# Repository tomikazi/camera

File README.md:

# Overview
The project provides a high-quality and low-latency video stream using Raspberry Pi HQ camera while allowing control of 
the camera orientation on pan & tilt axes. The video stream can be viewed using any modern browser or mobile device.
The camera orientation can be controlled using several different means. On mobile devices, it can be controlled using
touch swipe gestures or by moving the mobile device in 3D space. On desktop or laptop computers, the keyboard or mouse
drag gestures can be used.

The project is an adaptation of the [131/h264-live-player](https://github.com/131/h264-live-player) project. It differs
from the original project in number of ways, with the most important distinction being that the camera code is structured
as a client that connects to a broker, which is capable of brokering connections to multiple cameras and allows
multiple viewers to view the same camera.

This arrangement is better suited for deployment of cameras behind firewalls.

The video stream from the camera can be viewed on any modern browser. The pan/tilt can be controlled using several 
different means.

* Using mouse click-and-drag or tap-and-drag on touch devices
* Using arrow keyboard keys and other keyboard short-cuts  
* Using mobile device motion - works for iOS devices and select Androids that support `DeviceMotionEvent` Web API
    * Note that this requires the broker to use HTTPS

The pan and tilt mechanism uses A4988 stepper drivers and NEMA 17 motors to move about a Raspberry Pi HQ camera.
The current mount design allows for -180/+180 degrees on pan axis and -50/+50 degrees on tilt axis. Two hall-effect
sensors are used as limit sensors to allow for auto-homing the mount.

Note that this adaptation mangles the original by removing the alternate forms of streaming, instead focusing
solely on supporting the `raspvid` live stream.

# Installation of Broker Software
The broker is required as it is the only means of acquiring the video stream. For simple setup, it can be installed on
the same Raspberry Pi as the camera software. 

```
# Install or update the camera broker software
curl -s https://raw.githubusercontent.com/tomikazi/camera/master/tools/install-broker.sh | sh

# Setup the camera broker software to run as a daemon
curl -s https://raw.githubusercontent.com/tomikazi/camera/master/tools/install-broker-service.sh | sudo sh
```

Once started, the broker will listen on port 6000 for incoming WebSocket connections from the cameras and on port 5000 
for incoming HTTP requests and WebSocket connections from viewers. To expose HTTPS, it's probably easiest to use Apache 2
and setup redirect using URL re-writing. (_TODO: Add docs on this_)

# Installation of Camera Software
Use the following steps to install or update the camera software:

```
# Install or update the camera software
curl -s https://raw.githubusercontent.com/tomikazi/camera/master/tools/install-camera.sh | sh

# Setup the camera software to run as a daemon
curl -s https://raw.githubusercontent.com/tomikazi/camera/master/tools/install-camera-service.sh | sudo sh -s CAMERA-NAME [BROKER-URL]
```

Once started, the software will trigger auto-homing sequence and attempt WebSocket connection on port 6000 to the broker.
After the connection is established, the `raspivid` will be spawned and its video stream will be sent over the WebSocket
to the broker, from where it can be sent to the current viewers, be recorded or processed in some manner.

# Simple Token Authorization
The broker supports a simple token-based authorization scheme that allows securing access to the camera streams so that
only the users that know the camera name and a valid access token can access the video stream.

To enable the scheme, create a `tokens` file in the directory where the broker is installed. The format of the file
is as follows:

```
# userName: cameraName token
tom: FrontYard c11559d8-e91c-4140-85f0-9e14b4744e7e
tom: BackYard 329f1a1b-5c8d-40ab-9148-434f84312821
tom: Driveway 7a247b22-7bd8-4b27-8e1c-404fea90b615
guest: FrontYard 4ceb02b3-a0e9-4989-b1ff-72c3aac973ae
guest: Driveway a5217204-133d-4b39-900f-2222c962b535
```
The token is expected to be the standard 36 character UUID (see `uuidgen`). Presently, the user name is not used for
anything other than token management via the provided `ptcam-auth` script, which has the following usage:

```
usage: ptcam-auth <camera> list
       ptcam-auth <camera> <name>
       ptcam-auth <camera> grant <name>
       ptcam-auth <camera> revoke <name>
```

# Launching Viewer
To view a particular camera video stream, simply connect to the broker URL on port 5000 and specify the camera name and 
if security is required, the camera token, e.g.:

```
http://192.168.1.79:5000/camera/?id=FrontYard&t=c11559d8-e91c-4140-85f0-9e14b4744e7e
```

This will provide the web-page with the video stream canvas. The following is an example of the GUI when viewed on an
iOS device and with the camera positions shortcut menu activated:

The pan/tilt position and range indicator box is shown at the bottom and will be visible only when the camera is in motion.
You can see a brief [demo of the camera operation on YouTube](https://youtu.be/4mN1LiofYqg).

# REST API
The broker also supports a simple [REST API](/docs/api.md) using which other applications can query and control the remote cameras.

# Design
Additional design documentation for the 3D-printed mount, custom PCB and overall assembly can is available in the [Design](docs/design.md) section

# Credits to the original h264 project authors
* [131](mailto:131.js@cloudyks.org)
* [Broadway](https://github.com/mbebenita/Broadway)
* [urbenlegend/WebStreamer](https://github.com/urbenlegend/WebStreamer)

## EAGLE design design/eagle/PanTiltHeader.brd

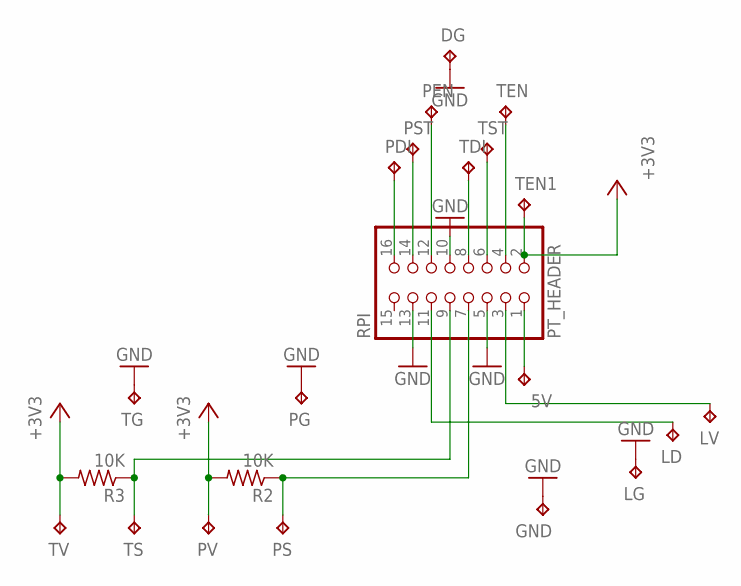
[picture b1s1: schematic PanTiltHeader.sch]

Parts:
5V: TPPAD1-13Y; P1-13Y
DG: TPPAD1-13Y; P1-13Y
GND: TPPAD1-13Y; P1-13Y
LD: TPPAD1-13Y; P1-13Y
LG: TPPAD1-13Y; P1-13Y
LV: TPPAD1-13Y; P1-13Y
PDI: TPPAD1-13Y; P1-13Y
PEN: TPPAD1-13Y; P1-13Y
PG: TPPAD1-13Y; P1-13Y
PS: TPPAD1-13Y; P1-13Y
PST: TPPAD1-13Y; P1-13Y
PT_HEADER: RPI; 2X08
PV: TPPAD1-13Y; P1-13Y
R2, R3: 10K; 0204/7
TDI: TPPAD1-13Y; P1-13Y
TEN, TEN1: TPPAD1-13Y; P1-13Y
TG: TPPAD1-13Y; P1-13Y
TS: TPPAD1-13Y; P1-13Y
TST: TPPAD1-13Y; P1-13Y
TV: TPPAD1-13Y; P1-13Y

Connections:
+3V3: PT_HEADER.2, PV.TP, R2.2, R3.2, TEN1.TP, TV.TP
GND: DG.TP, GND.TP, LG.TP, PG.TP, PT_HEADER.5, PT_HEADER.10, PT_HEADER.13, TG.TP
unnamed: PT_HEADER.4, TEN.TP
unnamed: PT_HEADER.6, TST.TP
unnamed: PT_HEADER.8, TDI.TP
unnamed: PT_HEADER.9, R3.1, TS.TP
unnamed: PEN.TP, PT_HEADER.12
unnamed: PST.TP, PT_HEADER.14
unnamed: PDI.TP, PT_HEADER.16
unnamed: 5V.TP, PT_HEADER.1
unnamed: LV.TP, PT_HEADER.3
unnamed: PS.TP, PT_HEADER.7, R2.1
unnamed: LD.TP, PT_HEADER.11

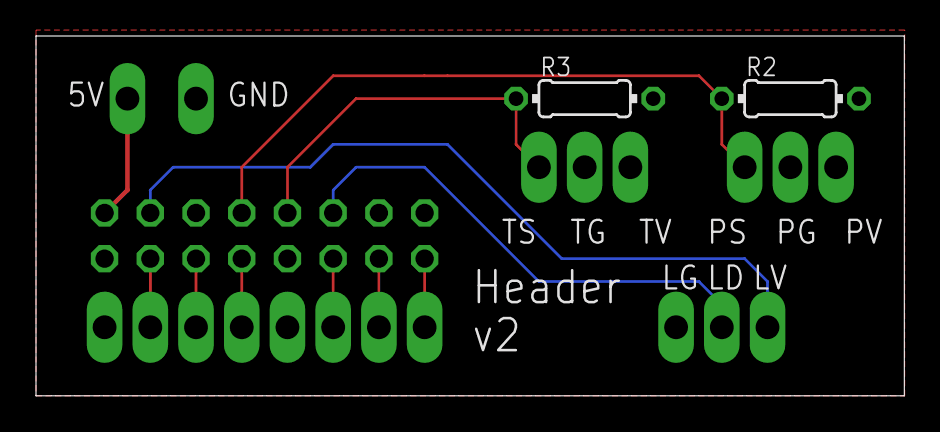
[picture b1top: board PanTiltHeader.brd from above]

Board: 2 copper layers, 48.2 x 20.0 mm, 22 parts (1 on the bottom side), 13 nets.

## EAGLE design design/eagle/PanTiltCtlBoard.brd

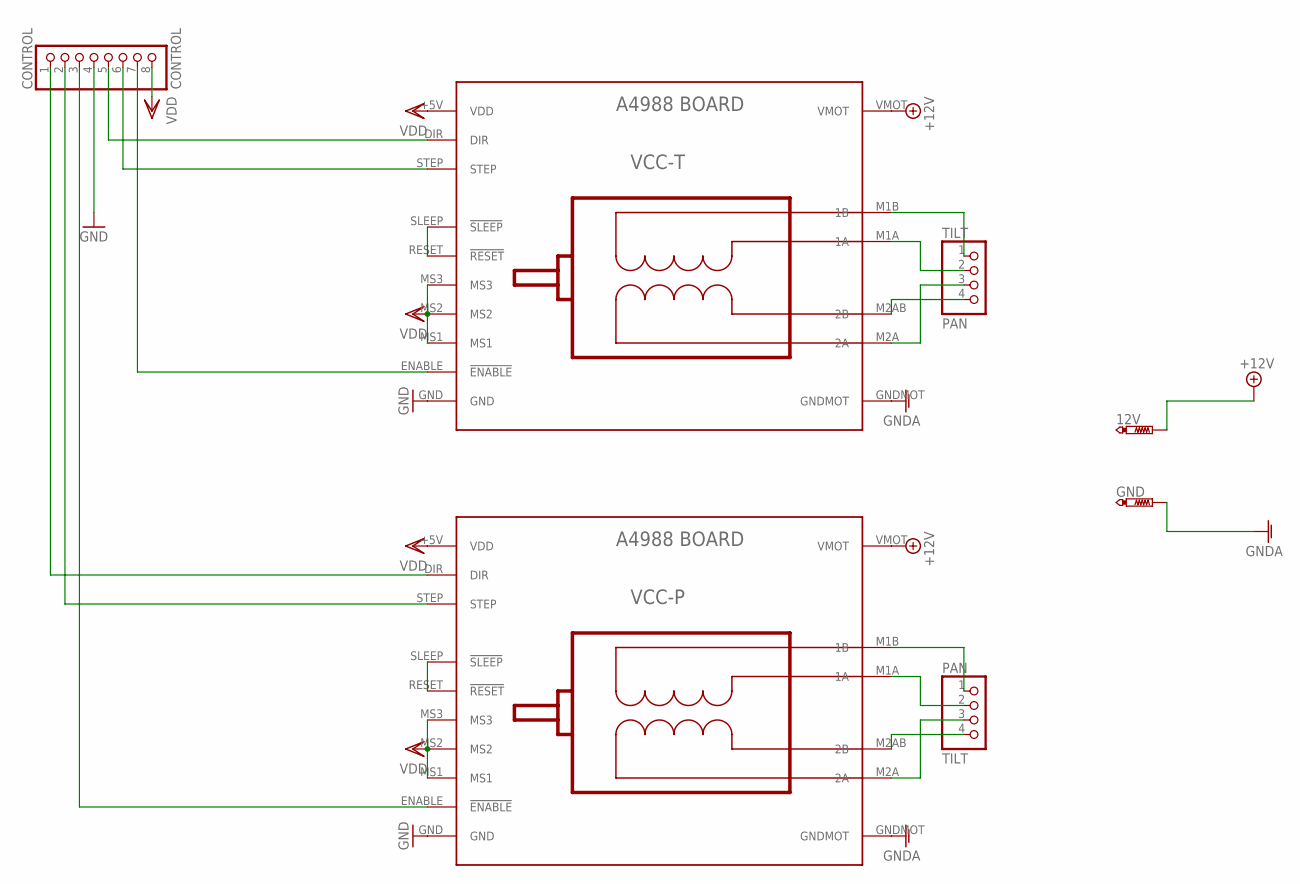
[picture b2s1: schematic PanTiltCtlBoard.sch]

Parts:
12V: PTR1PAD1-13Y; P1-13Y
CONTROL: CONTROL; 1X08
GND: PTR1PAD1-13Y; P1-13Y
PAN: TILT; 1X04
TILT: PAN; 1X04
VCC-P: BOARD_A4988
VCC-T: BOARD_A4988

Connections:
+12V: 12V.TP, VCC-P.VMOT, VCC-T.VMOT
GND: CONTROL.4, VCC-P.GND, VCC-T.GND
GNDA: GND.TP, VCC-P.GNDMOT, VCC-T.GNDMOT
unnamed: TILT.4, VCC-T.M2AB (2B)
unnamed: VCC-T.RESET (!RESET), VCC-T.SLEEP (!SLEEP)
unnamed: CONTROL.7, VCC-T.ENABLE (!ENABLE)
unnamed: CONTROL.6, VCC-T.STEP
unnamed: CONTROL.5, VCC-T.DIR
unnamed: CONTROL.1, VCC-P.DIR
unnamed: CONTROL.2, VCC-P.STEP
unnamed: CONTROL.3, VCC-P.ENABLE (!ENABLE)
unnamed: VCC-P.RESET (!RESET), VCC-P.SLEEP (!SLEEP)
unnamed: TILT.3, VCC-T.M2A (2A)
unnamed: TILT.1, VCC-T.M1B (1B)
unnamed: TILT.2, VCC-T.M1A (1A)
unnamed: PAN.4, VCC-P.M2AB (2B)
unnamed: PAN.3, VCC-P.M2A (2A)
unnamed: PAN.1, VCC-P.M1B (1B)
unnamed: PAN.2, VCC-P.M1A (1A)
VDD: CONTROL.8, VCC-P.+5V (VDD), VCC-P.MS1, VCC-P.MS2, VCC-P.MS3, VCC-T.+5V (VDD), VCC-T.MS1, VCC-T.MS2, VCC-T.MS3

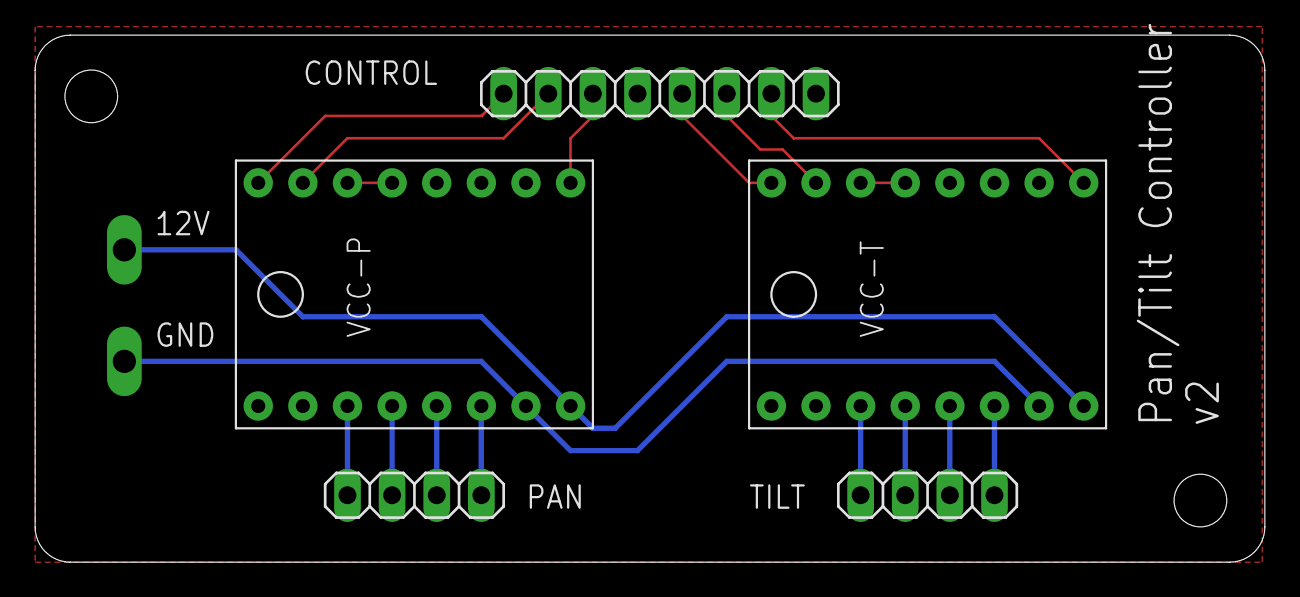
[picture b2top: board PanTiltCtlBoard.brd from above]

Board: 2 copper layers, 70.0 x 30.0 mm, 7 parts (0 on the bottom side), 20 nets.

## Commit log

2021-04-08 Initial commit; port from h264-live-player fork
2021-04-08 Renamed client to camera
2021-04-08 Adding install script for camera
2021-04-08 Adding installation scripts.
2021-04-08 Fixing broker service install
2021-04-08 More install tools tweaks.
2021-04-08 Fixed run-dev tools.
2021-04-08 Added auto-hiding of the position indicator to clean-up the GUI.
2021-04-09 Adding documentation.
2021-04-09 Fixed docs.
2021-04-09 More documentation refinements.
2021-04-09 Added REST API for query and control of the cameras.
2021-04-09 Added ability to retain current camera position.
2021-04-09 Refine the token authentication a bit.
2021-04-09 Fixed auth for HTTP access to work with duplicate tokens.
2021-04-10 Added photo of some of the part and custom boards.
2021-04-10 Fixed touch to work on Androids.
2021-04-11 Added dockerfile for broker.
2021-04-11 Moved tokens file to /var/broker to allow easier use with Docker volumes
2021-04-12 Added support for HW2 GPIO mappings.
2021-04-12 Added EAGLE files.
2021-04-12 Added Fusion 360 files.
2021-04-12 Fixed ptcam-auth default usage.
2021-04-16 Added smooth auto-hide for all UI elements.
2021-04-19 Added app icon.
2021-04-19 Added a link to the YouTube video demo.
2021-04-19 Fixed to work with the Tesla browser.
2021-04-21 Cropped app.png
2021-04-21 Updated API doc examples.
2021-04-22 Fixed ptcam-auth to reflect the change tokens file location.
2021-06-23 local testing
2021-06-23 capability to start, stop tracking
2021-06-23 improve tracking: smooth, scaled, no move small δ
2021-06-23 toggling tracking on desktop and mobile
2021-07-01 single client locking (via uuid)
2021-07-01 ignore calib images
2021-07-01 cli options to copy less, show help msg
2021-07-01 formatting
2021-07-01 newline
2021-07-01 remove random button, nicer tracking images
2021-07-01 fix a spelling mistake
2021-07-01 remove log
2021-07-01 tiny changes
2021-07-21 correct pan logic
2021-09-22 Title the page using camera ID; disable motion when not 'https:'
2021-10-13 Added ability for broker to record the camera streams
2021-10-19 Added ability to record; extracting SPS, PPS and sync NAL frames
2021-10-26 Added somple storage management for recordings
2021-11-09 Added ability to take a snapshot via API
2021-11-09 Lightened up the docker image and added ffmpeg to it
2021-11-09 Added REST API for list recordings and downloading them
2021-11-09 Changed snapshot API
2021-11-10 Added permissions check to the new APIs
2021-12-14 Added ability to control pan/tilt speed via API
2021-12-14 Christmas train mod; allows control and tracking
2021-12-19 Added option for the train to go indefinitely.
2022-01-07 Added secrets to gitignore
2022-02-01 Reworked to use servos instead of steppers to simplify HW setup
2022-02-01 Added shortcuts for extreme positions; consolidated processing
2022-02-01 Added ability to set default home position that is not 0,0
2022-02-01 Added ability to run camera client in no-video mode; only for pan/tilt control
2022-02-08 Pruned package dependencies
2022-02-08 Added support for long duration moves with linear/quad/cubic easing
2022-02-09 Updated docs, enhanced REST API, limited upwards tilt
2022-02-11 Added ability to store arbitrarily named positions
2022-02-12 Added ability to record positions
2022-02-15 Added update of the feedback during async moves
2022-02-16 Fixed reporting of the initial position
2022-03-22 Adding ability to restart camera from viewer
2022-03-25 Made jquery JS files local to avoid requirement for internet access.
